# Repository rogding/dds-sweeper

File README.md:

# dds-sweeper

Raspberry Pi Pico interface for the AD9959 DDS.

If you use this project, please cite as:

E. Huegler, J. C. Hill, and D. H. Meyer, An agile radio-frequency source using internal sweeps of a direct digital synthesizer,
*Review of Scientific Instruments*, **94**, 094705 (2023)
[https://doi.org/10.1063/5.0163342](https://doi.org/10.1063/5.0163342)

## Specs

- The timing capabilities of the DDS-Sweeper are tied to the number of clock cycles the pico takes to send the next instruction.  

| Table Mode      | 1 Channel | 2 Channel | 3 Channel | 4 Channel |
|-----------------|-----------|-----------|-----------|-----------|
| Single Stepping | 500       | 750       | 1000      | 1250      |
| Sweep Mode      | 1000      | 1500      | 2000      | 2500      |

- At the default Pico Clock frequency of 125 MHz those clock cycle counts correspond to the following times:  

| Table Mode      | 1 Channel | 2 Channel  | 3 Channel  | 4 Channel  |
|-----------------|-----------|------------|------------|------------|
| Single Stepping | 4 $\mu s$ | 6  $\mu s$ | 8  $\mu s$ | 10 $\mu s$ |
| Sweep Mode      | 8 $\mu s$ | 12 $\mu s$ | 16 $\mu s$ | 20 $\mu s$ |

- The number of instructions you can store in the table depends on the type of sweep being performed, the number of channels being used, and the pico chip version. We allocated a maximum ram size of:

244 kB (RP 2040):

| Table Mode                  | 1 Channel | 2 Channel | 3 Channel | 4 Channel |
|-----------------------------|-----------|-----------|-----------|-----------|
| Single Stepping (Ext Timer) | 16656     | 8615      | 5810      | 4383      |
| Sweep Mode (Ext Timer)      | 8614      | 4382      | 2938      | 2210      |
| Single Stepping (Int Timer) | 5000      | 5000      | 5000      | 4032      |
| Sweep Mode (Int Timer)      | 5000      | 4032      | 2703      | 2033      |

500 kB (RP 2350):

| Table Mode                  | 1 Channel | 2 Channel | 3 Channel | 4 Channel |
|-----------------------------|-----------|-----------|-----------|-----------|
| Single Stepping (Ext Timer) | 34132     | 17654     | 11905     | 8981      |
| Sweep Mode (Ext Timer)      | 17654     | 8981      | 6022      | 4529      |
| Single Stepping (Int Timer) | 5000      | 5000      | 5000      | 5000      |
| Sweep Mode (Int Timer)      | 5000      | 5000      | 5000      | 4353      |

## How to flash the firmware

Download the latest [dds-sweeper_rp2040.uf2 file for Pi Pico](https://github.com/QTC-UMD/dds-sweeper/releases/latest/download/dds-sweeper_rp2040.uf2) or [dds-sweeper_rp2350.uf2 file for Pi Pico 2](https://github.com/QTC-UMD/dds-sweeper/releases/latest/download/dds-sweeper_rp2350.uf2).
On your Raspberry Pi Pico, hold down the "bootsel" button while plugging the Pico into USB port on a PC (that must already be turned on).
The Pico should mount as a mass storage device (if it doesn't, try again or consult the Pico documentation).
Drag and drop the `.uf2` file into the mounted mass storage device.
The mass storage device should unmount after the copy completes. Your Pico is now running the DDS Sweeper firmware!

## Usage

### Wiring

Here is a simplified wiring diagram showing the mapping between Pico pins and the AD9959.

In the `dds-sweeper-board` directory is a KiCAD project for a simple carrier board
with a socket that aligns directly to the header pins of the AD9959 Eval board.
It is a recommended design for ensuring quality high-speed communication signals between the Pico and AD9959.

This board has a 3-pin header for connecting 3.3V and 1.8V to the TB1 header of the AD9959 Eval board,
as well as an SMA connected 1.8V for connection to the `AVDD` analog output power supplies of the board.
Note that the `AVDD` connections for each channel are electrically connected by the AD9959 Eval PCB,
meaning the 1.8V can be daisy chained with more SMA cables to power the `BG_VDD` and `CLK_VDD` inputs.

### Setup

When the DDS Sweeper is started, configuration is required before it can be used. It is often good to begin with a `reset` command, which resets the AD9959.

First, the clock should be setup with the `setclock` command, followed by the `setmult` command.

Second, the number of channels should be configured with the `setchannels` command, which sets the number of dynamic channels, and leaves the remaining channels static.

Finally, the mode and timing should be setup with the `mode` command. The DDS Sweeper uses either discrete amplitude, frequency, and phase steps or sweeps of one parameter (possibly with steps of the other parameter) as its primitive instructions. The DDS Sweeper can then use internal timing (in which case it generates triggers internally after each step or sweep) or external timing (in which case it waits for external triggers).

### Program loading

Once setup is complete, instructions (steps or sweeps, depending on the mode) and timings can be loaded using the `set`, `seti`, or `setb` commands. In addition to output instructions, there are special stop and repeat instructions (which can only be loaded using `seti` and `setb`). With instructions are loaded, the address (order in which they are executed) is specified, so the order of loading need not match the order of execution. Timing is set per address, so it is common to all channels. The stop instruction ends program execution, while the repeat instruction restarts program execution from the beginning. Instructions are loaded into an uninitialized array, so skipping instruction addresses or failing to specify stop/repeat at the end of the program may result in undefined behavior.

### Execution

Finally, the program can be executed using the `start` or `hwstart` commands. If termination of the program is required before it reaches a `stop` command, the `abort` command can be used.

## DDS Units

- Output Amplitude is dependent on frequency (some people on Analog Devices forum mentioned amplitude and frequency are related by a sinc function)

- The frequency resolution of the AD9959 is $= \frac{f_{sys clk}}{2^{32}}$. At the default system clock of 500 MHz, the frequency resolution is $\approx 0.1164$ Hz. Frequency input to the DDS Sweeper using the `set` command will be rounded to an integer multiple of the frequency resolution. Frequency input to the DDS Sweeper using the `seti` or `setb` commands will be in units of the frequency resolution.

- The phase resolution of the AD9959 is $= \frac{360^\circ}{2^{14}} \approx 0.02197^\circ$. Phase offsets given using the `set` command will be rounded to a multiple of this resolution. Phase offsets given using the `seti` or `setb` commands will be in units of this resolution.

- The amplitude resolution of the AD9959 is $= \frac{1}{2^{10}} \approx 0.09767\%$. Amplitude scale factors given using the `set` command will be rounded to a multiple of this resolution. Amplitude scale factors given using the `seti` or `setb` commands will be in units of this resolution.

- When the DDS Sweeper uses internal timing to execute instructions, that time is based on the number of clock cycles of the Pico's system clock (which defaults to 125 MHz for an 8 ns period). Timing inputs using the `set` command are given in seconds and will be rounded to an integer multiple of the Pico system clock period. Timing input using the `seti` or `setb` commands is defined to be in units of the Pico system clock period.

## Sweeps

- Setting up a sweep:  
  
Sweeps are defined by two parameters, sweep delta and ramp rate.
- Sweep Delta defines the change in output amplitude/frequency/phase on each sweep step
- Ramp rate defines how often a sweep step is taken. It is based off of the AD9959's sync clock signal which will be one quarter of the AD9959's system clock. The ramp rate parameter specifies the number of sync clock cycles per sweep step. A ramp rate of 1 will cause the sweep delta to be applied every 1 sync clock cycle. For upward sweeps, the ramp rate parameter can have a value of 1-255. For downward sweeps the ramp rate can only be 1.  

For more details on sweeps, see [sweep details](SWEEP_DETAILS.md).

## Serial API

Note: Commands must be terminated with `\n`.

### Status commands

- `version`:  
Responds with a string containing the firmware version.

- `status`:  
Returns the operating status of the DDS-Sweeper.

  - `0`: manual mode
  - `1`: transitioning to buffered execution
  - `2`: buffered execution
  - `3`: aborting buffered execution
  - `4`: last buffered execution was aborted
  - `5`: transitioning to manual mode

- `clkstatus`:
Returns the clocking status of the DDS-Sweeper as three numbers: `<int:mode> <double:freq> <int:mult>`.
Mode can be `0` for internal clocking or `1` for external clocking of the AD9959.
The frequency is the AD9959 reference frequency, in Hz.
`mult` is the AD9959 PLL multiplier. The corresponding system frequency is `freq*-*mult`.

- `board`:
Responds with which type of board the firmware is running on: `pico1` or `pico2`.

- `getfreqs`:  
Responds with a multi-line string containing the current operating frequencies of various clocks (you will be most interested in `pll_sys` and `clk_sys`). Multiline string ends with `ok\n`.

### State commands

- `start`:  
Starts buffered execution immediately.

- `hwstart`:  
Starts buffered execution once an external trigger is received.

- `abort`:  
Stops buffered execution immediately.

### Setup commands

- `setclock <mode:int> <freq:int> (<pll_mult:int>)`:  
Reconfigures the source/reference clock.
  - Mode `0`: Use pico system clock as reference to the AD9959.
    In this mode, the frequency provided also sets the pico system clock
    and it cannot exceed 133 MHz.
    The dds sweeper defaults to this mode with a frequency of 125 MHz and a PLL multiplier of 4.
  - Mode `1`: Sets the AD9959 to receive a reference clock not from the pico.
    Setting this mode does not change the pico system clock.

  `pll_mult` is an optional input that sets the AD9959's PLL multiplier on the Reference Clock input. The default value is 4, giving the AD9959 a system clock of 500 MHz with the pico's 125 MHz reference. Valid values are 1 or 4-20.  
  The AD9959's PLL has an output range of 100-160 MHz or 255-500 MHz with VCO gain enabled. The pico will automatically enable the VCO gain bit if the requested frequency is in the upper range. If trying to use the PLL multiplier to generate a frequency between 160 and 255 MHz, there is no guarantee of operation.

- `setchannels <num:int>`:  
Sets how many channels being used by the table mode. Uses the lowest channels first, starting with channel 0. If number of channels is set to `0`, buffered execution instructions will be written to all 4 channels simultaneously.

- `mode <sweep-type:int> <trigger-source:int>`:  
Configures what mode the DDS-Sweeper is operating in
  - 0: single stepping / manual mode
  - 1: amplitude sweep
  - 2: frequency sweep
  - 3: phase sweep
  - 4: amplitude sweep with frequency/phase steps
  - 5: frequency sweep with amplitude/phase steps
  - 6: phase sweep with frequency/amplitude steps  

  The operating mode must be set before buffered execution instructions can be programmed into the DDS-Sweeper.  
  A `trigger-source` of `0` means the Sweeper is expecting external triggers. A `trigger-source` of `1` means the Sweeper will send its own triggers and `set` commands will require an additional `time` argument.

### Manual output commands

- `setfreq <channel:int> <frequency:float>`:  
Manually set the output frequency of a specified channel. Channels are 0-3 and frequencies are in Hz. If `debug` is set to on, it will respond with the actual frequency set. The Sweeper must be in manual mode.

- `setphase <channel:int> <phase_offset:float>`:  
Manually set the phase offset of a specified channel. Channels are 0-3 and offsets are in degrees. If `debug` is set to on, it will respond with the actual degree offset set. The Sweeper must be in manual mode.

- `setamp <channel:int> <amplitude_scale_factor:float>`:  
Manually set the amplitude scale factor of a specified channel. Channels are 0-3 and amplitude scale factors are a precentage of the maximum output voltage. If `debug` is set to on, it will respond with the actual frequency set. The Sweeper must be in manual mode.

### Data loading commands

- `set`:  
Sets the value of instruction number `addr` for channel `channel` (zero indexed). `addr` starts at 0. It looks different depending on what mode the sweeper is in. If `Debug` is set to `on` it will respond with the actual values set for that instruction.
  - Single Stepping (mode 0): `set <channel:int> <addr:int> <frequency:float> <amplitude:float> <phase:float> (<time:float>)`
  - Sweep Mode (modes 1-3): `set <channel:int> <addr:int> <start_point:float> <end_point:float> <sweep_rate:float> (<time:float>)`

    `start_point` is the value the sweep should start from, and `end_point` is where it will stop. `sweep_rate` is the amount that the output should change in each quantity's units per second (further info below). In the AD9959, the sweep clock runs at one quarter the system clock. The types of values expected for `start_point`, `end_point`, and `sweep_rate` are different depending on the type of sweep:  
    - Amplitude Sweeps (mode 1)  
      `start_point` and `end_point` should be decimals between 0 and 1 that represent the desired proportion of the maximum output amplitude. `sweep_rate` is then that proportion per second. The resolution of the start and end values is $\frac{1}{1024} \approx 0.09766$.
    - Frequency Sweeps (mode 2)  
      `start_point` and `end_point` are frequencies in Hz, with `sweep_rate` in Hz per second. The start and end points can have decimal values, but they will be rounded to the nearest multiple of the frequency resolution ($\frac{f_{sysclk}}{2^{32}}$).
    - Phase Sweeps (mode 3)
      `start_point`, `end_point` are in degrees, with `sweep_rate` in degrees per second. The start and end points can have decimal values, but they will be rounded to the nearest multiple of the phase resolution ($\frac{360^\circ}{2^{14}} \approx 0.02197^\circ$).

  - Sweep and Single Stepping Mode (modes 4-6): `set <channel:int> <addr:int> <start_point:float> <end_point:float> <sweep_rate:float> <secondary1:double> <secondary2:double> (<time:float>)`

  These modes perform a linear sweep on one of the parameters, while simultaneously single stepping on the other two parameters.
  - Amplitude Sweeps (mode 4)  
    `secondary1` is the frequency, and `secondary2` is the phase offset.
  - Frequency Sweeps (mode 5)  
    `secondary1` is the amplitude scale factor, and `secondary2` is the phase offset.
  - Phase Sweeps (mode 6)  
    `secondary1` is the frequency, and `secondary2` is the amplitude scale factor.

- `seti`:  
Sets the value of instruction number `addr` for channel `channel` (zero indexed). `addr` starts at 0. It looks different depending on what mode the sweeper is in. If `Debug` is set to `on` it will respond with the actual values set for that instruction. `seti` uses integer values (AD9959 units) rather than floating point values. Otherwise, it is the same as `set`.
  - Single Stepping (mode 0): `seti <channel:int> <addr:int> <frequency:int> <amplitude:int> <phase:int> (<time:int>)`
  - Sweep Mode (modes 1-3): `seti <channel:int> <addr:int> <start_point:int> <end_point:int> <delta:int> <ramp-rate:int> (<time:int>)`

    `start_point` is the value the sweep should start from, and `end_point` is where it will stop. `delta` is the amount that the output should change by every cycle of the sweep clock. In the AD9959, the sweep clock runs at one quarter the system clock. `ramp-rate` is an additional divider that can applied to slow down the sweep clock further, must be in the range 1-255. The types of values expected for `start_point`, `end_point`, and `delta` different depending on the type of sweep  
    - Amplitude Sweeps (mode 1)  
      `start_point` and `end_point` should be integers between 0 and 1023 (inclusive).
    - Frequency Sweeps (mode 2)  
      `start_point`, `end_point`, and `delta` are integers between 0 and $2^{32} - 1$ in units of system clock rate (typically $500$ MHz) over $2^{32}$.
    - Phase Sweeps (mode 3)
      `start_point`, `end_point`, and `delta` are between 0 and 65535 (inclusive).

  - Sweep and Single Stepping Mode (modes 4-6): `set <channel:int> <addr:int> <start_point:int> <end_point:int> <delta:int> <ramp-rate:int> <secondary1:int> <secondary2:int> (<time:int>)`

    These modes perform a linear sweep on one of the parameters, while simultaneously single stepping on the other two parameters.
    - Amplitude Sweeps (mode 4)  
      `secondary1` is the frequency, and `secondary2` is the phase offset.
    - Frequency Sweeps (mode 5)  
      `secondary1` is the amplitude scale factor, and `secondary2` is the phase offset.
    - Phase Sweeps (mode 6)  
      `secondary1` is the frequency, and `secondary2` is the amplitude scale factor.

- `setb <start address:int> <instruction count:int>`:  
Bulk setting of instructions in binary. `start address` is the address of the first instruction loaded. `instruction count` instructions will be programmed. If there is not sufficient space for that many instructions, the response will be an error message. Otherwise, the response will be `ready for <byte count:int> bytes`, where `byte count` is the number of bytes the device is expecting. An array of instructions can then be transmitted. Note that all active channels are loaded together. The layout of the instruction array is mode dependent, and in the table below each mode is assumed to use external timing (where internal timing bytes are in parentheses and the dtype list must have `, ('time', '<u4')` appended)

| Mode  | Bytes per channel per instruction  | np.dtype  |
|---| :---: |:---:|
| Single Stepping (mode 0)  | 8 (12) | `[('frequency', '<u4'), ('amplitude', '<u2'), ('phase', '<u2')]`  |
| Amplitude Sweeps (mode 1)  | 7 (11) |  `[('start_amplitude', '<u2'), ('stop_amplitude', '<u2'), ('delta', '<u2'), ('rate', '<u1')]` |
| Frequency Sweeps (mode 2) | 13 (17) |  `[('start_frequency', '<u4'), ('stop_frequency', '<u4'), ('delta', '<u4'), ('rate', '<u1')]` |
| Phase Sweeps (mode 3)  | 7 (11) | `[('start_phase', '<u2'), ('stop_phase', '<u2'), ('delta', '<u2'), ('rate', '<u1')]` |
| Amplitude Sweep and Single Stepping (mode 4) | 13 (17)  | `[('start_amplitude', '<u2'), ('stop_amplitude', '<u2'), ('delta', '<u2'), ('rate', '<u1'), ('frequency', '<u4'), ('phase', '<u2')]`  |
| Frequency Sweep and Single Stepping (mode 5) | 17 (21) | `[('start_frequency', '<u4'), ('stop_frequency', '<u4'), ('delta', '<u4'), ('rate', '<u1'), ('amplitude', '<u2'), ('phase', '<u2')]`  |
| Phase Sweep and Single Stepping (mode 6)  | 13 (17) | `[('start_phase', '<u2'), ('stop_phase', '<u2'), ('delta', '<u2'), ('rate', '<u1'), ('frequency', '<u4'), ('amplitude', '<u2')]`  |

### Flash commands

- `save`:  
Saves the buffered execution table to nonvolatile memory so that it can be recovered later (after a power cycle).

- `load`:  
Retrieves the buffered execution table stored in nonvolatile memory and restores it to system memory so that it can be run. A saved table must be loaded before it can be run.

### Debugging commands

- `debug <state:str>`:  
Turns on extra debug messages printed over serial. `state` should be `on` or `off` (no string quotes required). On by default.

- `numtriggers`:  
Responds with the number of triggers processed since the last call of `start`

- `program`:  
Reboots the Pi Pico into firmware flashing mode. Serial will immediately disconnect and a mass storage device should appear.

## Compiling the firmware

If you want to make changes to the firmware, or want to compile it yourself (because you don't trust binary blobs from the internet), we provide a docker configuration to help you do that.

1. Install docker desktop and make sure it is running (if you are on Windows, you may have to mess around a bit to get virtualisation working at an operating system level)
2. Clone this repository
3. Open a terminal with the current working directory set to the repository root (the `docker-compose.yaml`` file should be there)
4. Run `docker compose build --pull` to build the docker container
5. Run `docker compose up` to build the PrawnBlaster firmware.

Step 4 will take a while as it has to build the docker container.
If it is slow to download packages from the Ubuntu package repositories, consider providing an explicit apt mirror that is fast for you: `docker compose build --pull --build-arg APT_MIRROR="http://azure.archive.ubuntu.com/ubuntu/"`.

If you want to change which version of the pico SDK it builds against, this is set in the `build/docker/Dockerfile` file.
Just change the git tag of the pico SDK that gets cloned out by git, then rebuild the docker container (see step 4).

Note once the docker container is built, you can run step 5 as many times as you like.
You do not need to rebuild the container, even if you make changes to the PrawnBlaster source code.
You only need to rebuild the docker container if you modify the `build/docker/Dockerfile` file.

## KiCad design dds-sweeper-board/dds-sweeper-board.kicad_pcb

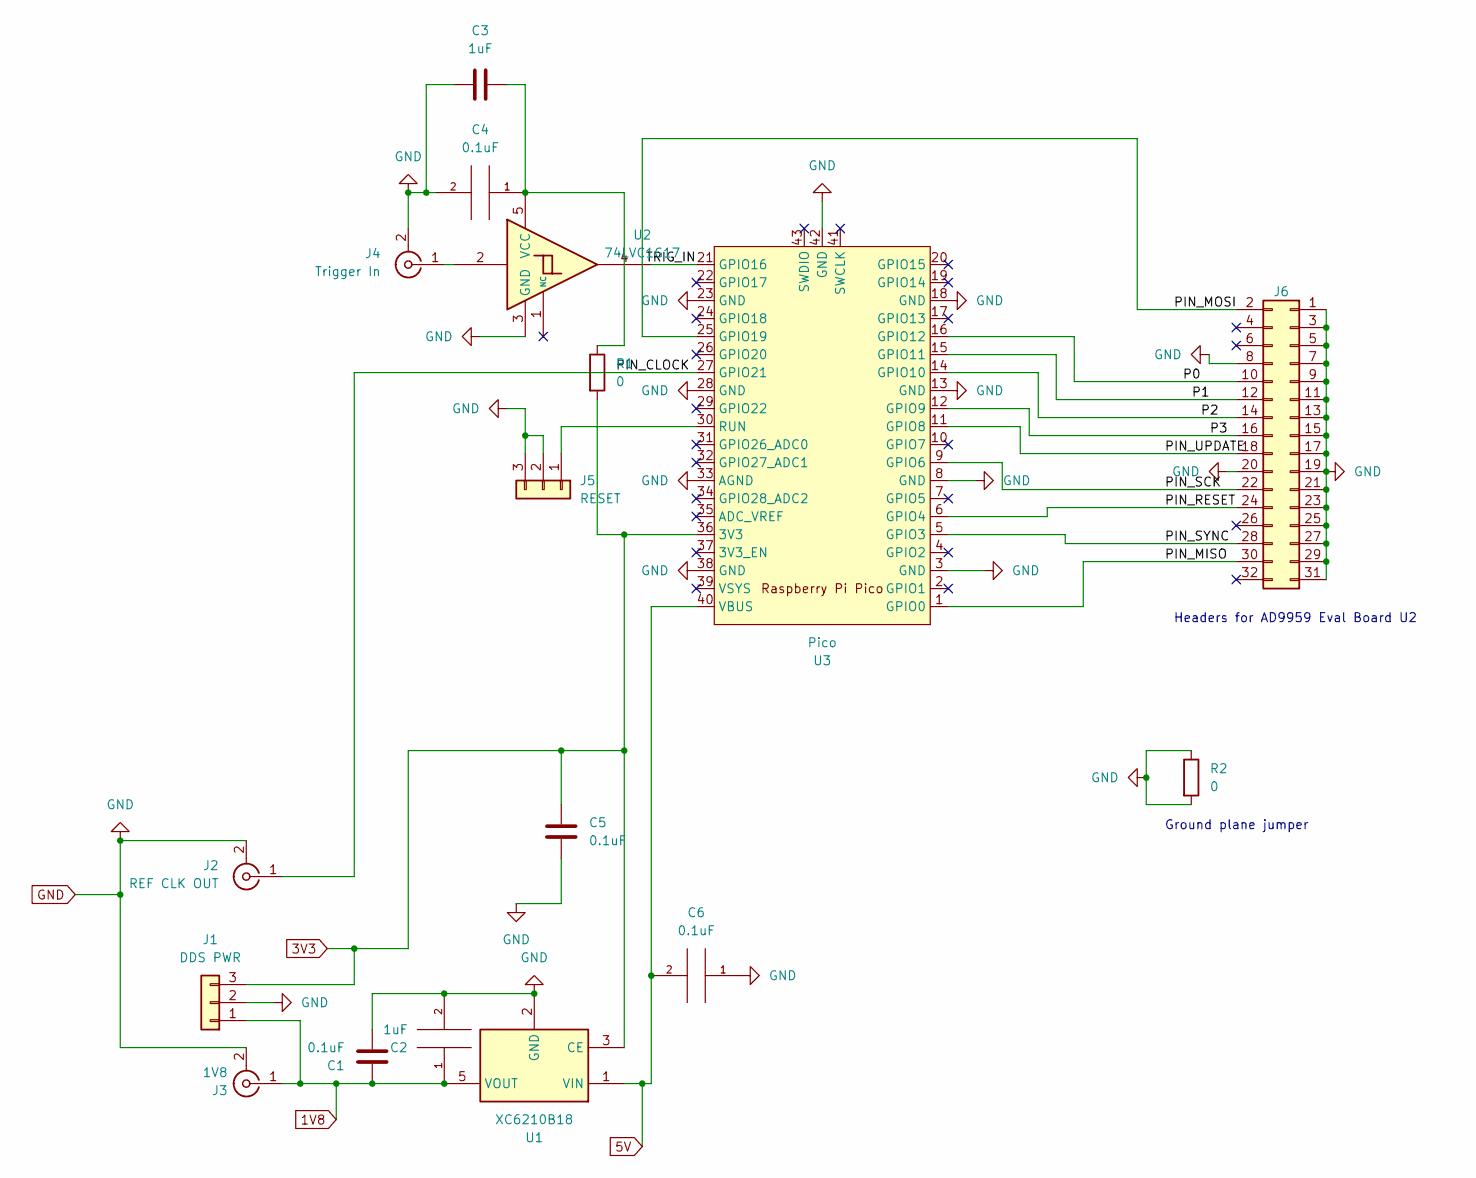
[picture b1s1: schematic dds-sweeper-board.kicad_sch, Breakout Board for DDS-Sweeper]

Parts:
C1, C4, C5, C6: 0.1uF; C_0805_2012Metric_Pad1.18x1.45mm_HandSolder
C2, C3: 1uF; C_0805_2012Metric_Pad1.18x1.45mm_HandSolder
J1: DDS PWR; PinHeader_1x03_P2.54mm_Vertical
J2: REF CLK OUT; SMA_Samtec_SMA-J-P-X-ST-EM1_EdgeMount
J3: 1V8; SMA_Samtec_SMA-J-P-X-ST-EM1_EdgeMount
J4: Trigger In; SMA_Samtec_SMA-J-P-X-ST-EM1_EdgeMount
J5: RESET; PinHeader_1x03_P2.54mm_Vertical
J6: AD9959 Eval Header; PinSocket_2x16_P2.54mm_Vertical
R1, R2: 0; R_1206_3216Metric_Pad1.30x1.75mm_HandSolder
U1: XC6210B18; SOT-23-5
U2: 74LVC1G17; SOT-23-5
U3: Pico; RPi_Pico_SMD

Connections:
1V8: C1.1, C2.1, J1.1, J3.1 (In), U1.5 (VOUT)
3V3: C5.2, J1.3, R1.2, U1.3 (CE), U3.36 (3V3)
5V: C6.2, U1.1 (VIN), U3.40 (VBUS)
/P0: J6.10, U3.16 (GPIO12)
/P1: J6.12, U3.15 (GPIO11)
/P2: J6.14, U3.14 (GPIO10)
/P3: J6.16, U3.12 (GPIO9)
/PIN_CLOCK: J2.1 (In), U3.27 (GPIO21)
/PIN_MISO: J6.30, U3.1 (GPIO0)
/PIN_MOSI: J6.2, U3.25 (GPIO19)
/PIN_RESET: J6.24, U3.6 (GPIO4)
/PIN_SCK: J6.22, U3.9 (GPIO6)
/PIN_SYNC: J6.28, U3.5 (GPIO3)
/PIN_UPDATE: J6.18, U3.11 (GPIO8)
/TRIG_IN: U2.4, U3.21 (GPIO16)
GND: C1.2, C2.2, C3.2, C4.2, C5.1, C6.1, J1.2, J2.2 (Ext), J3.2 (Ext), J4.2 (Ext), J5.2, J5.3, J6.1, J6.3, J6.5, J6.7, J6.8, J6.9, J6.11, J6.13, J6.15, J6.17, J6.19, J6.20, J6.21, J6.23, J6.25, J6.27, J6.29, J6.31, R2.1, R2.2, U1.2 (GND), U2.3 (GND), U3.3 (GND), U3.8 (GND), U3.13 (GND), U3.18 (GND), U3.23 (GND), U3.28 (GND), U3.33 (AGND), U3.38 (GND), U3.42 (GND)
unnamed: J4.1 (In), U2.2
unnamed: J5.1, U3.30 (RUN)
unnamed: C3.1, C4.1, R1.1, U2.5 (VCC)

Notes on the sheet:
Headers for AD9959 Eval Board U2
Ground plane jumper

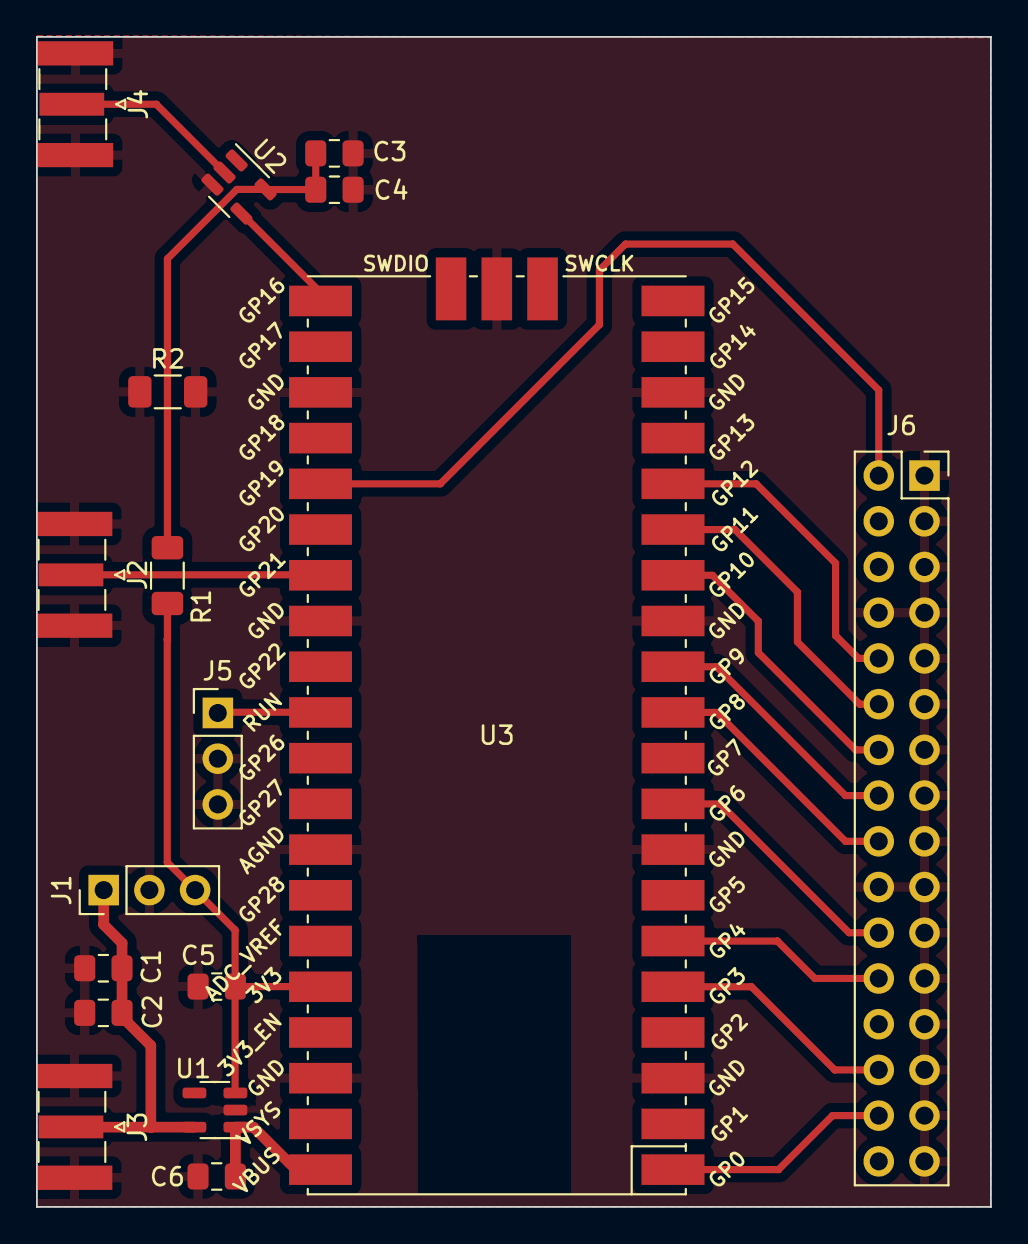
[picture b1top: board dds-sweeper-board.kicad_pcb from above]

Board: 2 copper layers, 53.0 x 65.0 mm, 17 parts (0 on the bottom side), 19 nets.

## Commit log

2025-09-19 Update breakout board to have an input buffer on the trigger line.
    Should help with longer cable runs on the trigger input.
2025-10-17 Update KiCAD project with proper header footprint (instead of sockets) and add 3D components so 3D board render is correct.
2025-10-17 Add polished wiring diagram to README along with 3D render of breakout board.
    Include section in README about wiring up the board.
2025-10-18 Update wiring diagram to be less confusing about the CLK input direction
